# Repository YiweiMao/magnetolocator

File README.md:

# magnetolocator

Check here to see our progress:
Hackathon Force Feedback VR Glove
https://docs.google.com/document/d/1uaAP13nhqvj-tF6IxJNAysReoOo3x5oB9gJD-OO6OQ0/edit

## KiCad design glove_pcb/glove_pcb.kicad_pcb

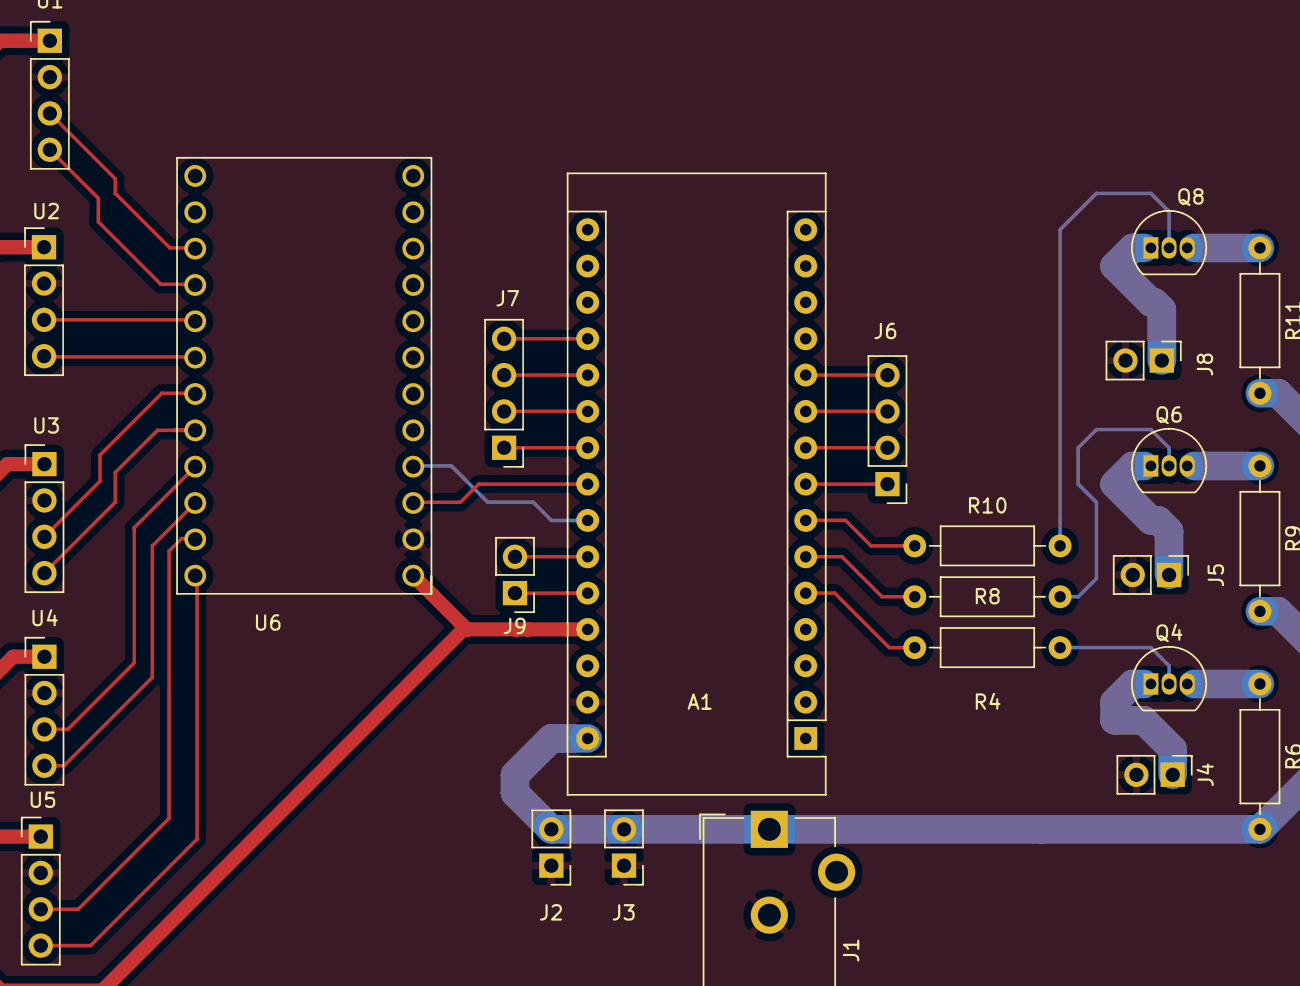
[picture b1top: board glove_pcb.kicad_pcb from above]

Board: 2 copper layers, 25 parts (0 on the bottom side), 37 nets.

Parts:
A1: Arduino_Nano_v3.x; Arduino_Nano
J1: Barrel_Jack; BarrelJack_CUI_PJ-102AH_Horizontal
J2: Exposed power and ground; PinHeader_1x02_P2.54mm_Vertical
J3: Alternate power ground inputs; PinHeader_1x02_P2.54mm_Vertical
J4, J5, J8, J9: Conn_01x02_Male; PinHeader_1x02_P2.54mm_Vertical
J6, J7: Conn_01x04_Male; PinHeader_1x04_P2.54mm_Vertical
Q4, Q6, Q8: PN2222A; TO-92_Inline
R4, R8, R10: 220; R_Axial_DIN0207_L6.3mm_D2.5mm_P10.16mm_Horizontal
R6, R9, R11: 10; R_Axial_DIN0207_L6.3mm_D2.5mm_P10.16mm_Horizontal
U1, U2, U3, U4, U5: magnetometer_connect; PinHeader_1x04_P2.54mm_Vertical
U6: TCA9548Amultiplex; TCA9548A_multiplex

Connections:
GND: A1.29, J1.2, J2.1, J3.1, J4.2, J5.2, J8.2, U1.2, U2.2, U3.2, U4.2, U5.2, U6.2
unnamed: A1.5, R4.1
unnamed: A1.6, R8.1
unnamed: A1.7, R10.1
unnamed: A1.8, J6.1
unnamed: A1.9, J6.2
unnamed: A1.10, J6.3
unnamed: A1.11, J6.4
unnamed: A1.19, J7.4
unnamed: A1.20, J7.3
unnamed: A1.21, J7.2
unnamed: A1.22, J7.1
unnamed: A1.23, U6.3
unnamed: A1.24, U6.4
unnamed: A1.25, J9.2
unnamed: A1.26, J9.1
unnamed: A1.27, U1.1, U2.1, U3.1, U4.1, U5.1, U6.1
unnamed: J4.1, Q4.1
unnamed: J5.1, Q6.1
unnamed: J8.1, Q8.1
unnamed: Q4.2, R4.2
unnamed: Q4.3, R6.1
unnamed: Q6.2, R8.2
unnamed: Q6.3, R9.1
unnamed: Q8.2, R10.2
unnamed: Q8.3, R11.1
unnamed: U1.3, U6.22
unnamed: U1.4, U6.21
unnamed: U2.3, U6.20
unnamed: U2.4, U6.19
unnamed: U3.3, U6.18
unnamed: U3.4, U6.17
unnamed: U4.3, U6.16
unnamed: U4.4, U6.15
unnamed: U5.3, U6.14
unnamed: U5.4, U6.13
VCC: A1.30, J1.1, J2.2, J3.2, R6.2, R9.2, R11.2

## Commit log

2020-01-25 got someone else's curve fit library compiling
2020-01-25 updated README with gDoc link.
2020-01-25 Basic mag read outs
2020-01-25 added notebook FFT code
2020-01-25 Reading serial
2020-01-25 added custom magnetometer cpp file for high performace
2020-01-25 reports all mag info on one line
2020-01-26 frequency interrupts added
2020-02-29 added state to struct becuase Jack was angry at me
2020-02-29 electromag and magnetometer in classes
2020-02-29 added frequency rates for all electro mags
2020-02-29 refactored structure
2020-02-29 Changed folders
2020-02-29 Made code nice, still don't know if it compiles
2020-02-29 Compiles now!!!
2020-02-29 Got readings and coils working but dies soon yeet
2020-03-02 pcbs for yw
2020-04-23 added pcb files
2020-05-07 updated pcb
